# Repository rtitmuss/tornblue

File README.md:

# TornBlue - a bluetooth split keyboard

In this repo you can find information about the TornBlue a bluetooth split keyboard with SMT components. This is an iteration on the [Torn](https://github.com/rtitmuss/torn), which is a split keyboard using through hole components.

You can ask questions and get help on the [Torn Discord channel](https://discord.gg/mamAqNccju).

**WARNING: These files are provided as a reference for designing keyboard PCBs, without liability and without any guarantees regarding functionality. This is untested work in progress, really don't assume anything here will work.**

## Features

- nRF52840 using [zmk](https://zmk.dev/) keyboard firmware
- Battery charging for a 3.7v lithium rechargeable battery (JST-PH connector)
- 6x3 or 5x3 layout with detachable outer column
- 3 leds and 1 charging led
-  ([SOIC test clip footprint](https://hackaday.com/2019/06/13/soicbite-a-program-debug-connector-for-an-soic-test-clip/)) for programming
- Breakout with switchable 3.3v and gpios
- Battery level reported over BT
- Supports soldered Cherry MX compatible or Kailh Choc key switches
- Horizontal reset button (case friendly) 
- JLCPCB PCBA (pcb assembly); handsoldering required for underglow leds and JST-PH connector 

Optional features:

- Underglow leds 
- Optional Panasonic EVQWGD001 wheel encoders

## Parts required

- 2x assembled TornBlue Rev 1 PCBs
- 2x 3.7v lithium rechargeable battery with JST connector. **SAFETY NOTE: Only use a LiIon battery with over-charging and over-use protection. Check the battery polarity before connecting.**
- (Optional) 2x [JST-PH connector](https://www.electrokit.com/en/product/header-ph-2p-2mm-right-angle-smd/). 2mm pitch. Side entry. Surface-mounted.
- (Optional) 2 x [Panasonic EVQWGD001](https://www.aliexpress.com/wholesale?catId=0&initiative_id=SB_20210830111528&SearchText=Panasonic+EVQWGD001) wheel encoder
- (Optional) 12 x [WS2812B 5050 leds](https://www.aliexpress.com/wholesale?catId=0&initiative_id=SB_20210830111716&SearchText=WS2812B)
- (Optional) ST link v2 (or similar) and SOIC-8 test clip for programming the bootloader

## Build instructions

You can find full [build instructions](./build.md), and information for [different cases](./case/README.md).

## Components

The main components are:

- [Holyiot YJ-18010](http://www.holyiot.com/tp/2019042516322180424.pdf); this was chosen as it has castellated edges, which is easier hand soldering the module to the PCB.

- [XC6220](https://www.torexsemi.com/file/xc6220/XC6220.pdf); 3.3V voltage regulator to supply the Holyiot module.

- [TP4096](https://dlnmh9ip6v2uc.cloudfront.net/datasheets/Prototyping/TP4056.pdf) Li-Ion Battery Charger 

- [SRV05-4](https://www.onsemi.com/pdf/datasheet/srv05-4-d.pdf) ESD protection for the USB port
   
 - Other parts use 0805 and SOT-23 packages. These larger packages can be hand soldered and are similar sizes for a pleasing appearance. The parts have been laid out horizontally with a consistent polarity to simplify assembly.

## Reference designs

The following projects were used as reference designs.

- [ZMK hardware design guide](https://github.com/ebastler/zmk-designguide) (CERN Open Hardware Licence Version 2 - Permissive) - note the battery charging circuit might be unsafe, see this information about [TP4056](https://www.best-microcontroller-projects.com/tp4056.html)

- [isometria75](https://github.com/ebastler/isometria-75/tree/v2) (BSD 2-Clause License)

- [Unified USB type-C PCB](https://github.com/ebastler/unified-usb-pcb) (BSD 2-Clause License)

- [Nice!Nano](https://nicekeyboards.com/docs/nice-nano/pinout-schematic)

- [nRFMicro](https://github.com/joric/nrfmicro/wiki) (Public domain)

- [Adafruit nRF52840](https://learn.adafruit.com/introducing-the-adafruit-nrf52840-feather/downloads) (Creative Commons Attribution, Share-Alike)

## Showcase

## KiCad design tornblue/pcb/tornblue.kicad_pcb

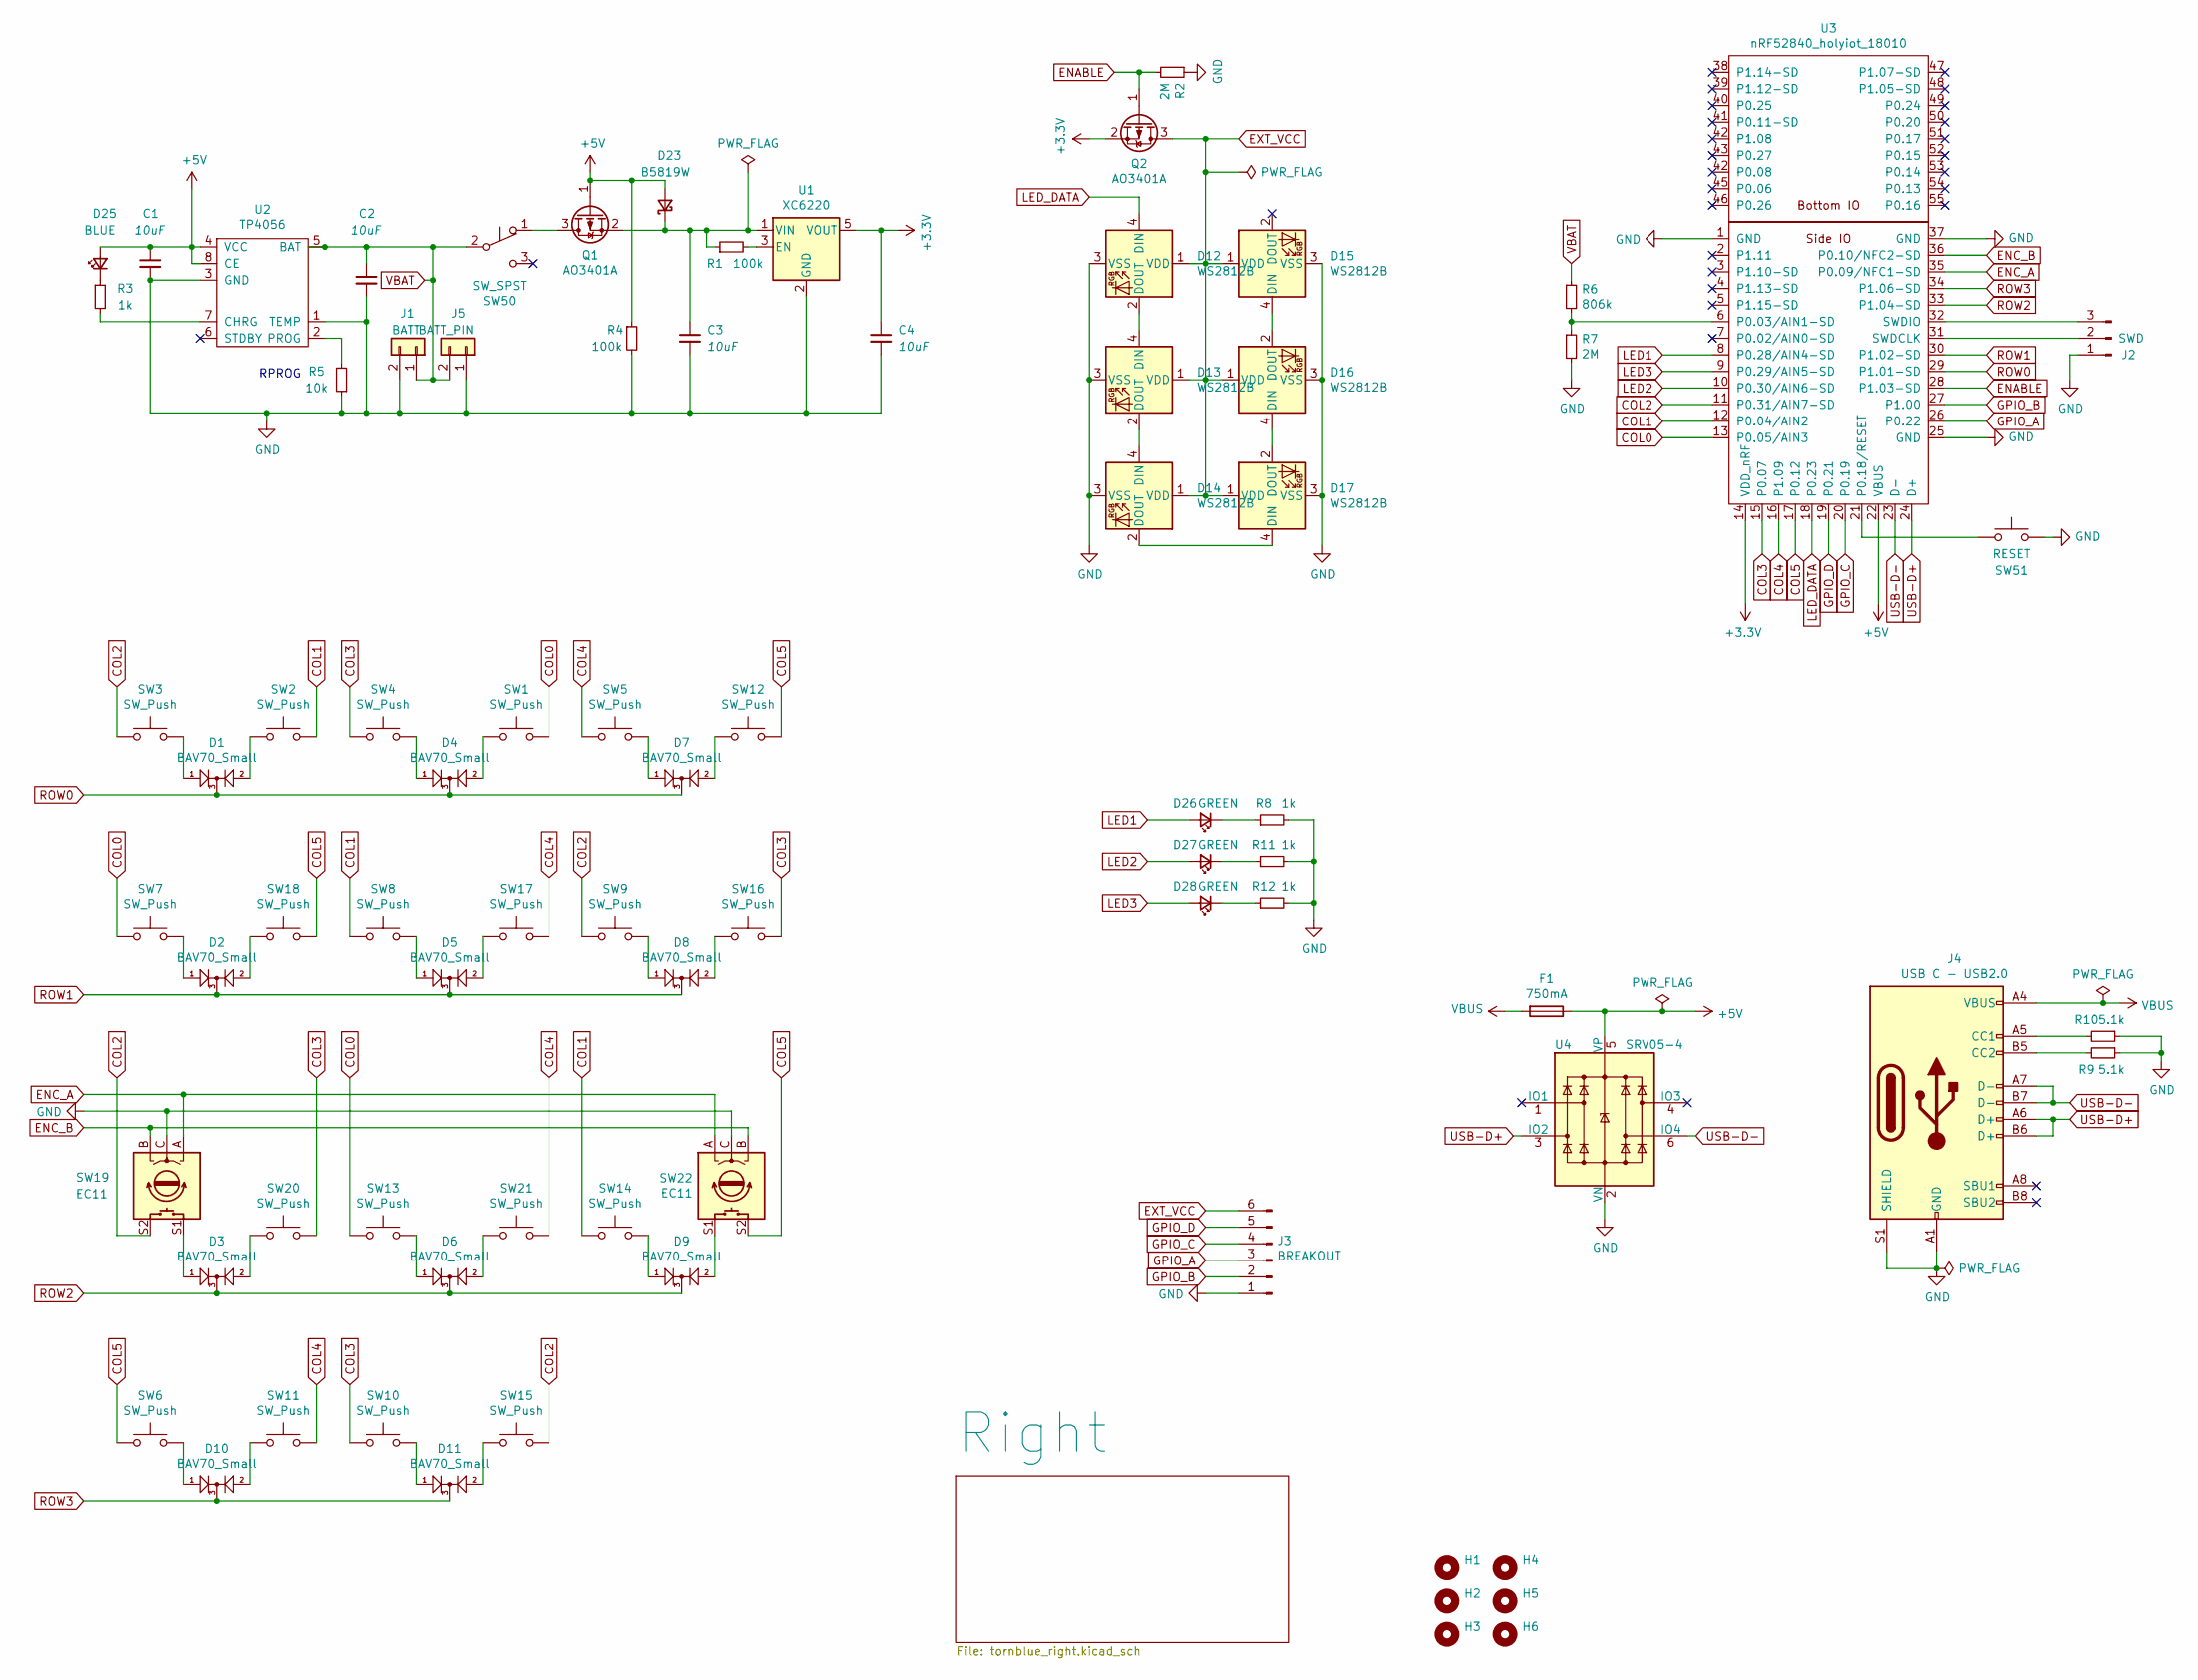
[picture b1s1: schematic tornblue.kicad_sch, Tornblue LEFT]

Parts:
C1, C2, C3, C4: 10uF; D_0805_2012Metric; LCSC C15850
D1, D2, D3, D4, D5, D6, D7, D8, D9, D10, D11: BAV70_Small; SOT-23; LCSC C68978
D12, D13, D14, D15, D16, D17: WS2812B; LED_WS2812B_PLCC4_5.0x5.0mm_P3.2mm; LCSC C2761795
D23: B5819W; D_SOD-123; LCSC C8598
D25: BLUE; LED_0805_2012Metric; LCSC C99870
D26, D27, D28: GREEN; LED_0805_2012Metric; LCSC C397047
F1: 750mA; Fuse_1206_3216Metric; LCSC C328915
H1, H2, H3, H4: MountingHole; MountingHole_3.2mm_M3_DIN965_Pad
H5, H6: MountingHole; MountingHole_3.2mm_M3_DIN965_Pad_Slot
J1: BATT; JST_PH_S2B-PH-SM4-TB_1x02-1MP_P2.00mm_Horizontal; LCSC C295747
J2: SWD; SOIC_clipProgSmall
J3: BREAKOUT; PinHeader_1x06_P1.27mm_Vertical
J4: USB C - USB2.0; USB_C_Receptacle_XKB_U262-16XN-4BVC11; LCSC C167321
J5: BATT_PIN; PinHeader_1x02_P2.54mm_Vertical
Q1, Q2: AO3401A; SOT-23; LCSC C15127
R1, R4: 100k; R_0805_2012Metric; LCSC C17407
R2, R7: 2M; R_0805_2012Metric; LCSC C26112
R3, R8, R11, R12: 1k; R_0805_2012Metric; LCSC C17513
R5: 10k; R_0805_2012Metric; LCSC C17414
R6: 806k; R_0805_2012Metric; LCSC C63494
R9, R10: 5.1k; R_0805_2012Metric; LCSC C27834
SW1, SW2, SW3, SW4, SW5, SW6, SW7, SW8, SW9, SW10, SW11, SW12, SW13, SW14, SW15, SW16, SW17, SW18, SW20, SW21: SW_Push; MX_PG1350_optional
SW19, SW22: EC11; MX_PG1350_EVQWGD001_LR_optional
SW50: SW_SPST; SW_SPDT_PCM12; LCSC C221841
SW51: RESET; SW_SPST_TS24CA; LCSC C393942
U1: XC6220; SOT-23-5; LCSC C86534
U2: TP4056; SOIC-8-1EP_3.9x4.9mm_P1.27mm_EP2.29x3mm_ThermalVias; LCSC C16581
U3: nRF52840_holyiot_18010; LCSC nRF52840_holyiot_18010
U4: SRV05-4; SOT-23-6; LCSC C85364

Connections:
+3V3: C4.1, Q2.2 (S), U1.5 (VOUT), U3.14 (VDD_nRF)
+5V: C1.1, D23.2 (A), D25.2 (A), F1.1, Q1.1 (G), R4.1, U2.4 (VCC), U2.8 (CE), U3.22 (VBUS), U4.5 (VP)
COL0: SW1.1, SW7.1, SW13.1, U3.13 (P0.05/AIN3)
COL1: SW2.1, SW8.1, SW14.1, U3.12 (P0.04/AIN2)
COL2: SW3.1, SW9.1, SW15.1, SW19.S2, U3.11 (P0.31/AIN7-SD)
COL3: SW4.1, SW10.1, SW16.1, SW20.1, U3.15 (P0.07)
COL4: SW5.1, SW11.1, SW17.1, SW21.1, U3.16 (P1.09)
COL5: SW6.1, SW12.1, SW18.1, SW22.S2, U3.17 (P0.12)
ENABLE: Q2.1 (G), R2.2, U3.28 (P1.03-SD)
ENC_A: SW19.A, SW22.A, U3.35 (P0.09/NFC1-SD)
ENC_B: SW19.B, SW22.B, U3.36 (P0.10/NFC2-SD)
EXT_VCC: D12.1 (VDD), D13.1 (VDD), D14.1 (VDD), D15.1 (VDD), D16.1 (VDD), D17.1 (VDD), J3.6, Q2.3 (D)
GND: C1.2, C2.2, C3.2, C4.2, D12.3 (VSS), D13.3 (VSS), D14.3 (VSS), D15.3 (VSS), D16.3 (VSS), D17.3 (VSS), J1.2, J2.1, J3.1, J4.A1 (GND), J4.A12 (GND), J4.B1 (GND), J4.B12 (GND), J4.S1 (SHIELD), J5.1, R2.1, R4.2, R5.1, R7.2, R8.2, R9.1, R10.1, R11.2, R12.2, SW19.C, SW22.C, SW51.2, U1.2 (GND), U2.1 (TEMP), U2.3 (GND), U3.1 (GND), U3.25 (GND), U3.37 (GND), U4.2 (VN)
GPIO_A: J3.3, U3.26 (P0.22)
GPIO_B: J3.2, U3.27 (P1.00)
GPIO_C: J3.4, U3.20 (P0.19)
GPIO_D: J3.5, U3.19 (P0.21)
LED1: D26.2 (A), U3.8 (P0.28/AIN4-SD)
LED2: D27.2 (A), U3.10 (P0.30/AIN6-SD)
LED3: D28.2 (A), U3.9 (P0.29/AIN5-SD)
LED_DATA: D12.4 (DIN), U3.18 (P0.23)
unnamed: C3.1, D23.1 (K), Q1.2 (S), R1.1, U1.1 (VIN)
unnamed: D1.1 (A1), SW3.2
unnamed: D1.2 (A2), SW2.2
unnamed: D2.1 (A1), SW7.2
unnamed: D2.2 (A2), SW18.2
unnamed: D3.1 (A1), SW19.S1
unnamed: D3.2 (A2), SW20.2
unnamed: D4.1 (A1), SW4.2
unnamed: D4.2 (A2), SW1.2
unnamed: D5.1 (A1), SW8.2
unnamed: D5.2 (A2), SW17.2
unnamed: D6.1 (A1), SW13.2
unnamed: D6.2 (A2), SW21.2
unnamed: D7.1 (A1), SW5.2
unnamed: D7.2 (A2), SW12.2
unnamed: D8.1 (A1), SW9.2
unnamed: D8.2 (A2), SW16.2
unnamed: D9.1 (A1), SW14.2
unnamed: D9.2 (A2), SW22.S1
unnamed: D10.1 (A1), SW6.2
unnamed: D10.2 (A2), SW11.2
unnamed: D11.1 (A1), SW10.2
unnamed: D11.2 (A2), SW15.2
unnamed: D12.2 (DOUT), D13.4 (DIN)
unnamed: D13.2 (DOUT), D14.4 (DIN)
unnamed: D14.2 (DOUT), D17.4 (DIN)
unnamed: D15.4 (DIN), D16.2 (DOUT)
unnamed: D16.4 (DIN), D17.2 (DOUT)
unnamed: D25.1 (K), R3.1
unnamed: D26.1 (K), R8.1
unnamed: D27.1 (K), R11.1
unnamed: D28.1 (K), R12.1
unnamed: J2.2, U3.31 (SWDCLK)
unnamed: J2.3, U3.32 (SWDIO)
unnamed: J4.A5 (CC1), R10.2
unnamed: J4.B5 (CC2), R9.2
unnamed: Q1.3 (D), SW50.1 (A)
unnamed: R1.2, U1.3 (EN)
unnamed: R3.2, U2.7 (CHRG)
unnamed: R5.2, U2.2 (PROG)
unnamed: R6.2, R7.1, U3.6 (P0.03/AIN1-SD)
unnamed: SW51.1, U3.21 (P0.18/RESET)
ROW0: D1.3 (K), D4.3 (K), D7.3 (K), U3.29 (P1.01-SD)
ROW1: D2.3 (K), D5.3 (K), D8.3 (K), U3.30 (P1.02-SD)
ROW2: D3.3 (K), D6.3 (K), D9.3 (K), U3.33 (P1.04-SD)
ROW3: D10.3 (K), D11.3 (K), U3.34 (P1.06-SD)
USB-D+: J4.A6 (D+), J4.B6 (D+), U3.24 (D+), U4.3 (IO2)
USB-D-: J4.A7 (D-), J4.B7 (D-), U3.23 (D-), U4.6 (IO4)
VBAT: C2.1, J1.1, J5.2, R6.1, SW50.2 (B), U2.5 (BAT)
VBUS: F1.2, J4.A4 (VBUS), J4.A9 (VBUS), J4.B4 (VBUS), J4.B9 (VBUS)

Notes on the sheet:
RPROG

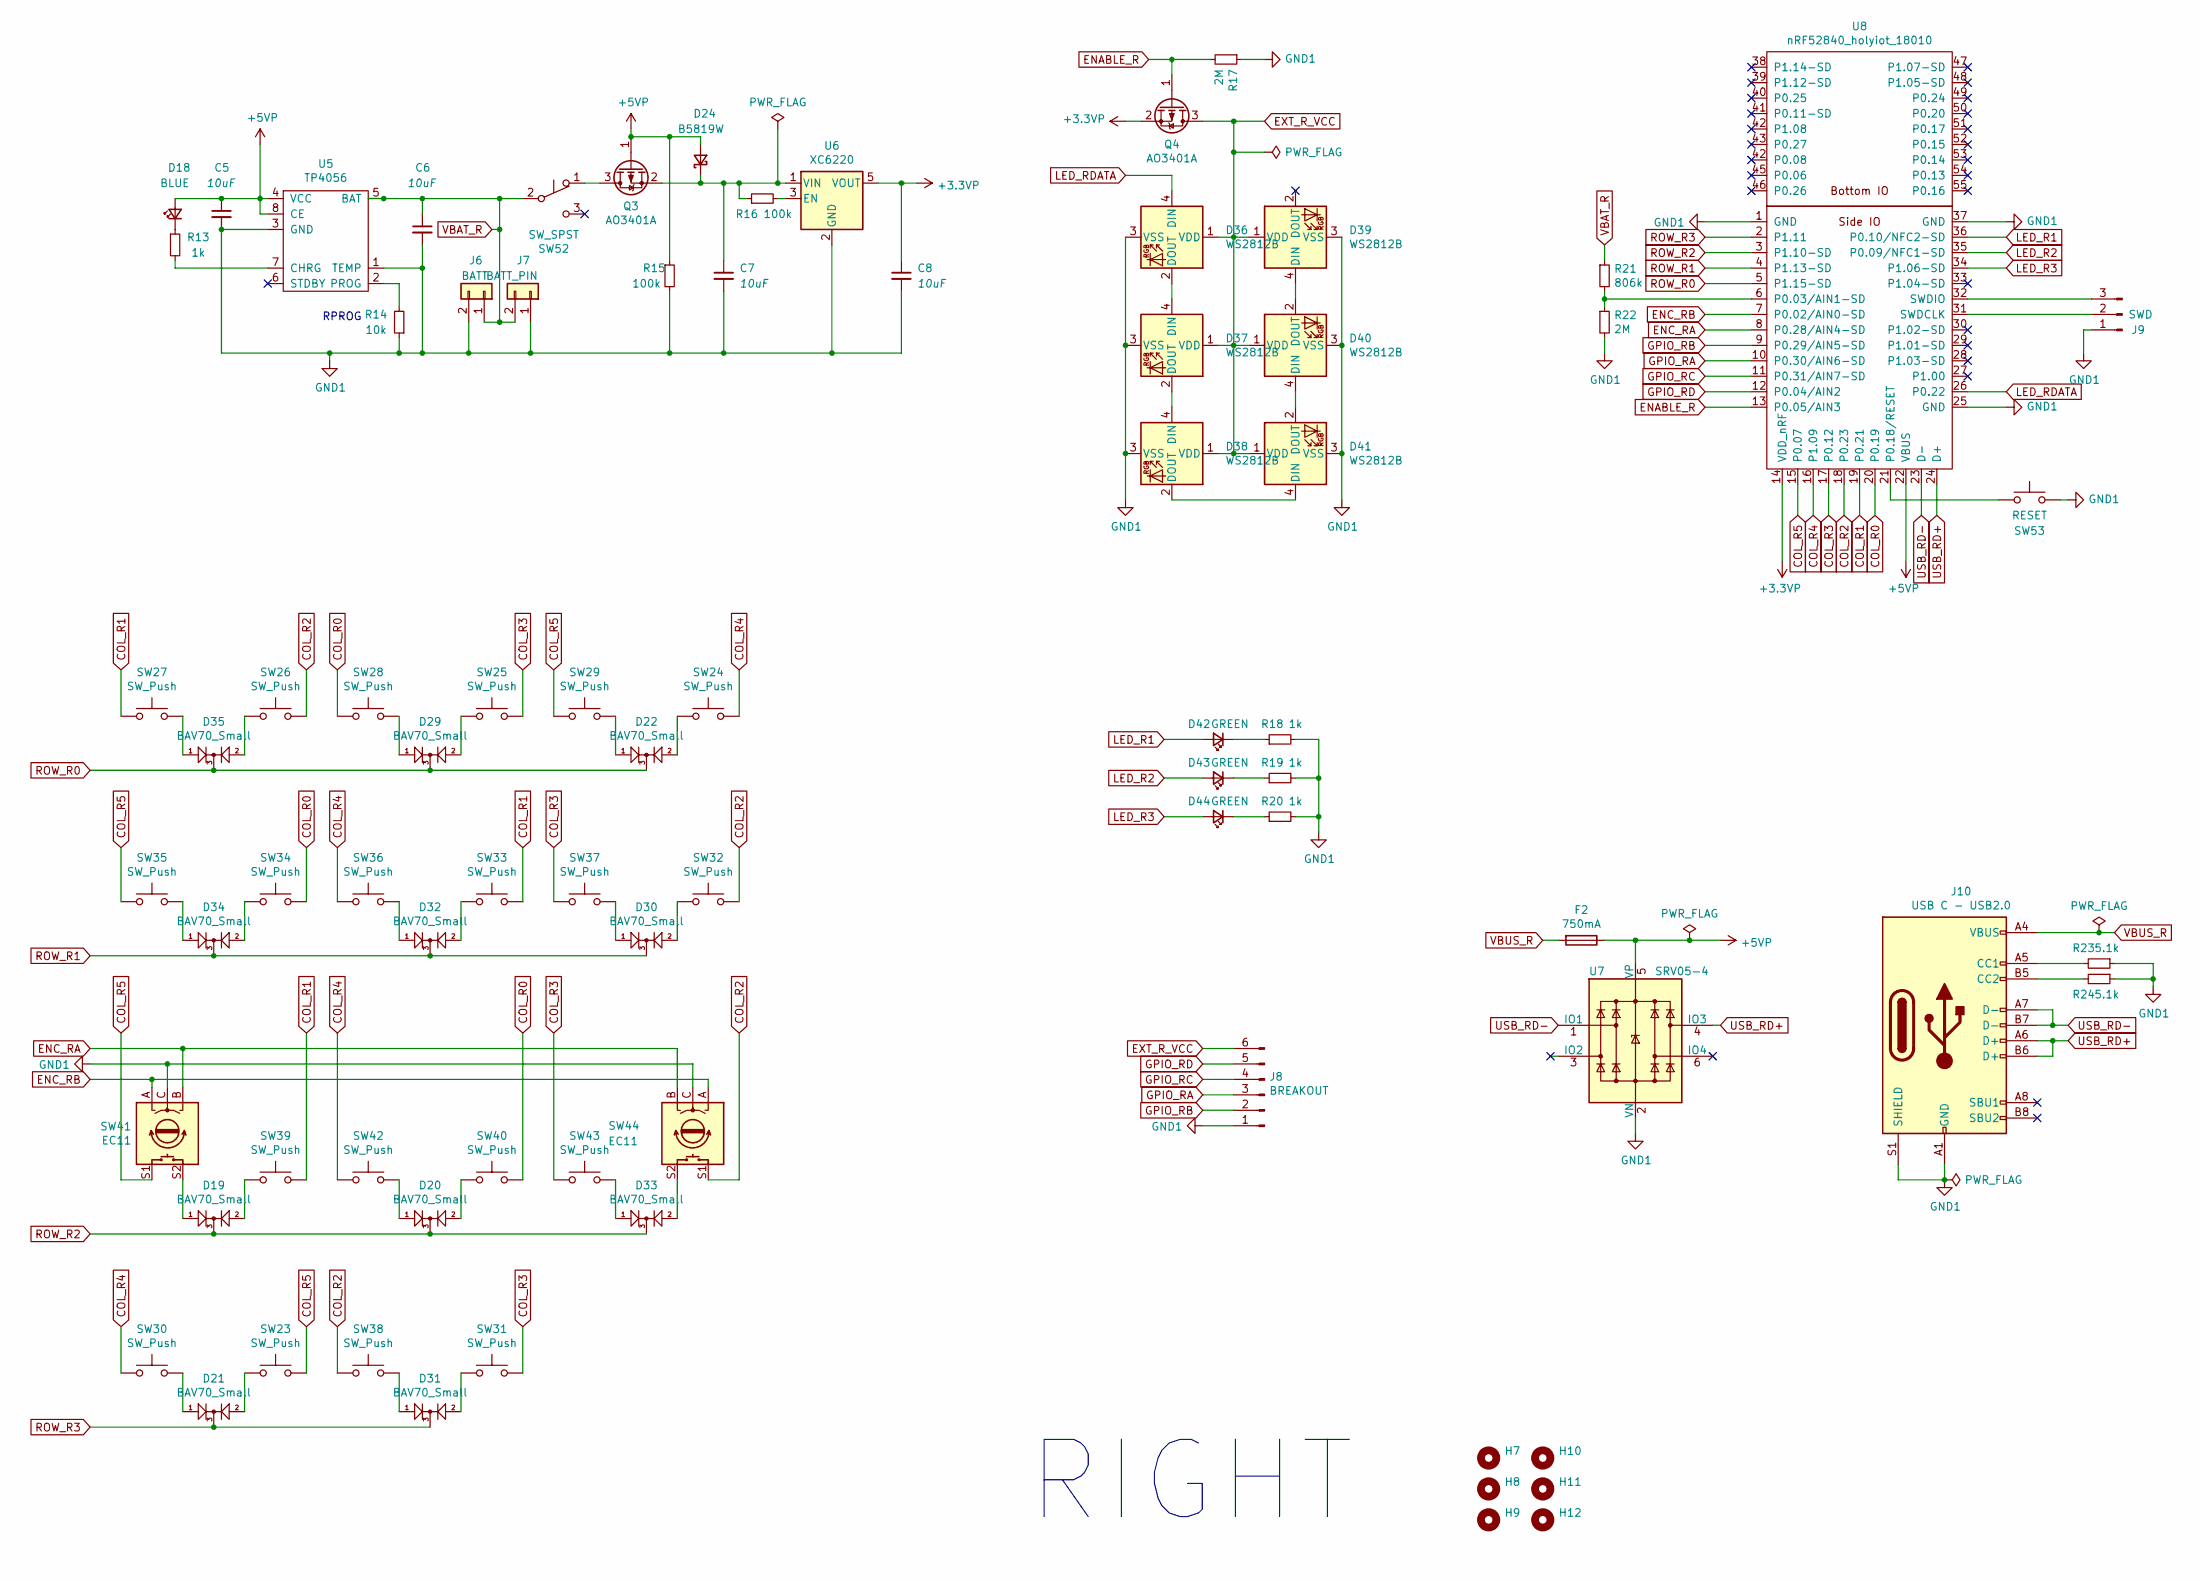
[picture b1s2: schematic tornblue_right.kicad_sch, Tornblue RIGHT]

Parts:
C5, C6, C7, C8: 10uF; D_0805_2012Metric; LCSC C15850
D18: BLUE; LED_0805_2012Metric; LCSC C99870
D19, D20, D21, D22, D29, D30, D31, D32, D33, D34, D35: BAV70_Small; SOT-23; LCSC C68978
D24: B5819W; D_SOD-123; LCSC C8598
D36, D37, D38, D39, D40, D41: WS2812B; LED_WS2812B_PLCC4_5.0x5.0mm_P3.2mm; LCSC C2761795
D42, D43, D44: GREEN; LED_0805_2012Metric; LCSC C397047
F2: 750mA; Fuse_1206_3216Metric; LCSC C328915
H7, H8, H9, H10: MountingHole; MountingHole_3.2mm_M3_DIN965_Pad
H11, H12: MountingHole; MountingHole_3.2mm_M3_DIN965_Pad_Slot
J6: BATT; JST_PH_S2B-PH-SM4-TB_1x02-1MP_P2.00mm_Horizontal; LCSC C295747
J7: BATT_PIN; PinHeader_1x02_P2.54mm_Vertical
J8: BREAKOUT; PinHeader_1x06_P1.27mm_Vertical
J9: SWD; SOIC_clipProgSmall
J10: USB C - USB2.0; USB_C_Receptacle_XKB_U262-16XN-4BVC11; LCSC C167321
Q3, Q4: AO3401A; SOT-23; LCSC C15127
R13, R18, R19, R20: 1k; R_0805_2012Metric; LCSC C17513
R14: 10k; R_0805_2012Metric; LCSC C17414
R15, R16: 100k; R_0805_2012Metric; LCSC C17407
R17, R22: 2M; R_0805_2012Metric; LCSC C26112
R21: 806k; R_0805_2012Metric; LCSC C63494
R23, R24: 5.1k; R_0805_2012Metric; LCSC C27834
SW23, SW24, SW25, SW26, SW27, SW28, SW29, SW30, SW31, SW32, SW33, SW34, SW35, SW36, SW37, SW38, SW39, SW40, SW42, SW43: SW_Push; MX_PG1350_optional
SW41, SW44: EC11; MX_PG1350_EVQWGD001_UD_optional
SW52: SW_SPST; SW_SPDT_PCM12; LCSC C221841
SW53: RESET; SW_SPST_TS24CA; LCSC C393942
U5: TP4056; SOIC-8-1EP_3.9x4.9mm_P1.27mm_EP2.29x3mm_ThermalVias; LCSC C16581
U6: XC6220; SOT-23-5; LCSC C86534
U7: SRV05-4; SOT-23-6; LCSC C85364
U8: nRF52840_holyiot_18010; LCSC nRF52840_holyiot_18010

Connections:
+3.3VP: C8.1, Q4.2 (S), U6.5 (VOUT), U8.14 (VDD_nRF)
+5VP: C5.1, D18.2 (A), D24.2 (A), F2.1, Q3.1 (G), R15.1, U5.4 (VCC), U5.8 (CE), U7.5 (VP), U8.22 (VBUS)
COL_R0: SW28.1, SW34.1, SW40.1, U8.20 (P0.19)
COL_R1: SW27.1, SW33.1, SW39.1, U8.19 (P0.21)
COL_R2: SW26.1, SW32.1, SW38.1, SW44.S1, U8.18 (P0.23)
COL_R3: SW25.1, SW31.1, SW37.1, SW43.1, U8.17 (P0.12)
COL_R4: SW24.1, SW30.1, SW36.1, SW42.1, U8.16 (P1.09)
COL_R5: SW23.1, SW29.1, SW35.1, SW41.S1, U8.15 (P0.07)
ENABLE_R: Q4.1 (G), R17.2, U8.13 (P0.05/AIN3)
ENC_RA: SW41.B, SW44.B, U8.8 (P0.28/AIN4-SD)
ENC_RB: SW41.A, SW44.A, U8.7 (P0.02/AIN0-SD)
EXT_R_VCC: D36.1 (VDD), D37.1 (VDD), D38.1 (VDD), D39.1 (VDD), D40.1 (VDD), D41.1 (VDD), J8.6, Q4.3 (D)
GND1: C5.2, C6.2, C7.2, C8.2, D36.3 (VSS), D37.3 (VSS), D38.3 (VSS), D39.3 (VSS), D40.3 (VSS), D41.3 (VSS), J6.2, J7.1, J8.1, J9.1, J10.A1 (GND), J10.A12 (GND), J10.B1 (GND), J10.B12 (GND), J10.S1 (SHIELD), R14.1, R15.2, R17.1, R18.2, R19.2, R20.2, R22.2, R23.1, R24.1, SW41.C, SW44.C, SW53.2, U5.1 (TEMP), U5.3 (GND), U6.2 (GND), U7.2 (VN), U8.1 (GND), U8.25 (GND), U8.37 (GND)
GPIO_RA: J8.3, U8.10 (P0.30/AIN6-SD)
GPIO_RB: J8.2, U8.9 (P0.29/AIN5-SD)
GPIO_RC: J8.4, U8.11 (P0.31/AIN7-SD)
GPIO_RD: J8.5, U8.12 (P0.04/AIN2)
LED_R1: D42.2 (A), U8.36 (P0.10/NFC2-SD)
LED_R2: D43.2 (A), U8.35 (P0.09/NFC1-SD)
LED_R3: D44.2 (A), U8.34 (P1.06-SD)
LED_RDATA: D36.4 (DIN), U8.26 (P0.22)
unnamed: C7.1, D24.1 (K), Q3.2 (S), R16.1, U6.1 (VIN)
unnamed: D18.1 (K), R13.1
unnamed: D19.1 (A1), SW41.S2
unnamed: D19.2 (A2), SW39.2
unnamed: D20.1 (A1), SW42.2
unnamed: D20.2 (A2), SW40.2
unnamed: D21.1 (A1), SW30.2
unnamed: D21.2 (A2), SW23.2
unnamed: D22.1 (A1), SW29.2
unnamed: D22.2 (A2), SW24.2
unnamed: D29.1 (A1), SW28.2
unnamed: D29.2 (A2), SW25.2
unnamed: D30.1 (A1), SW37.2
unnamed: D30.2 (A2), SW32.2
unnamed: D31.1 (A1), SW38.2
unnamed: D31.2 (A2), SW31.2
unnamed: D32.1 (A1), SW36.2
unnamed: D32.2 (A2), SW33.2
unnamed: D33.1 (A1), SW43.2
unnamed: D33.2 (A2), SW44.S2
unnamed: D34.1 (A1), SW35.2
unnamed: D34.2 (A2), SW34.2
unnamed: D35.1 (A1), SW27.2
unnamed: D35.2 (A2), SW26.2
unnamed: D36.2 (DOUT), D37.4 (DIN)
unnamed: D37.2 (DOUT), D38.4 (DIN)
unnamed: D38.2 (DOUT), D41.4 (DIN)
unnamed: D39.4 (DIN), D40.2 (DOUT)
unnamed: D40.4 (DIN), D41.2 (DOUT)
unnamed: D42.1 (K), R18.1
unnamed: D43.1 (K), R19.1
unnamed: D44.1 (K), R20.1
unnamed: J9.2, U8.31 (SWDCLK)
unnamed: J9.3, U8.32 (SWDIO)
unnamed: J10.A5 (CC1), R23.2
unnamed: J10.B5 (CC2), R24.2
unnamed: Q3.3 (D), SW52.1 (A)
unnamed: R13.2, U5.7 (CHRG)
unnamed: R14.2, U5.2 (PROG)
unnamed: R16.2, U6.3 (EN)
unnamed: R21.2, R22.1, U8.6 (P0.03/AIN1-SD)
unnamed: SW53.1, U8.21 (P0.18/RESET)
ROW_R0: D22.3 (K), D29.3 (K), D35.3 (K), U8.5 (P1.15-SD)
ROW_R1: D30.3 (K), D32.3 (K), D34.3 (K), U8.4 (P1.13-SD)
ROW_R2: D19.3 (K), D20.3 (K), D33.3 (K), U8.3 (P1.10-SD)
ROW_R3: D21.3 (K), D31.3 (K), U8.2 (P1.11)
USB_RD+: J10.A6 (D+), J10.B6 (D+), U7.4 (IO3), U8.24 (D+)
USB_RD-: J10.A7 (D-), J10.B7 (D-), U7.1 (IO1), U8.23 (D-)
VBAT_R: C6.1, J6.1, J7.2, R21.1, SW52.2 (B), U5.5 (BAT)
VBUS_R: F2.2, J10.A4 (VBUS), J10.A9 (VBUS), J10.B4 (VBUS), J10.B9 (VBUS)

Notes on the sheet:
RIGHT
RPROG

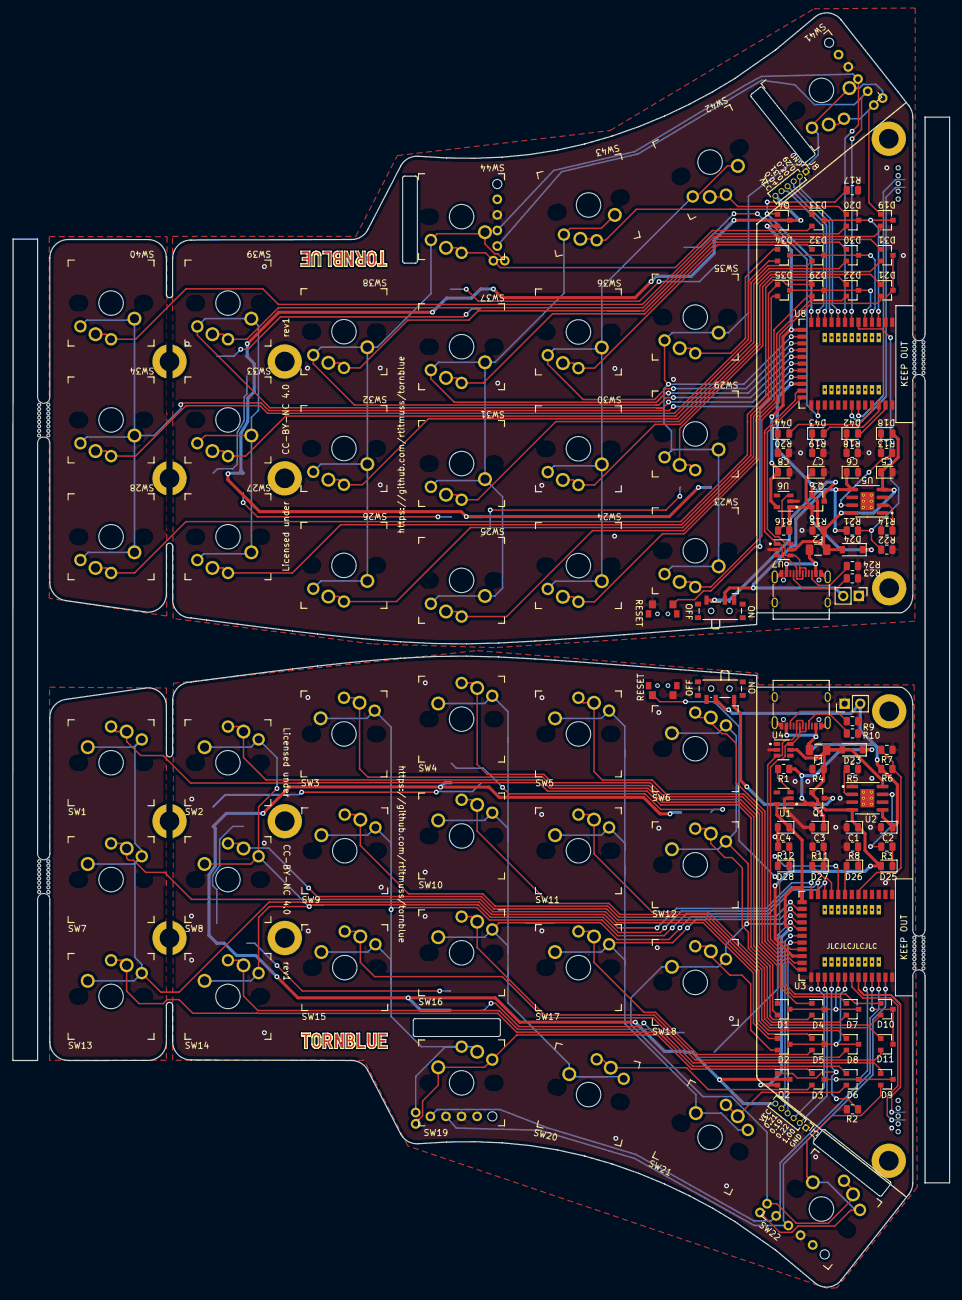
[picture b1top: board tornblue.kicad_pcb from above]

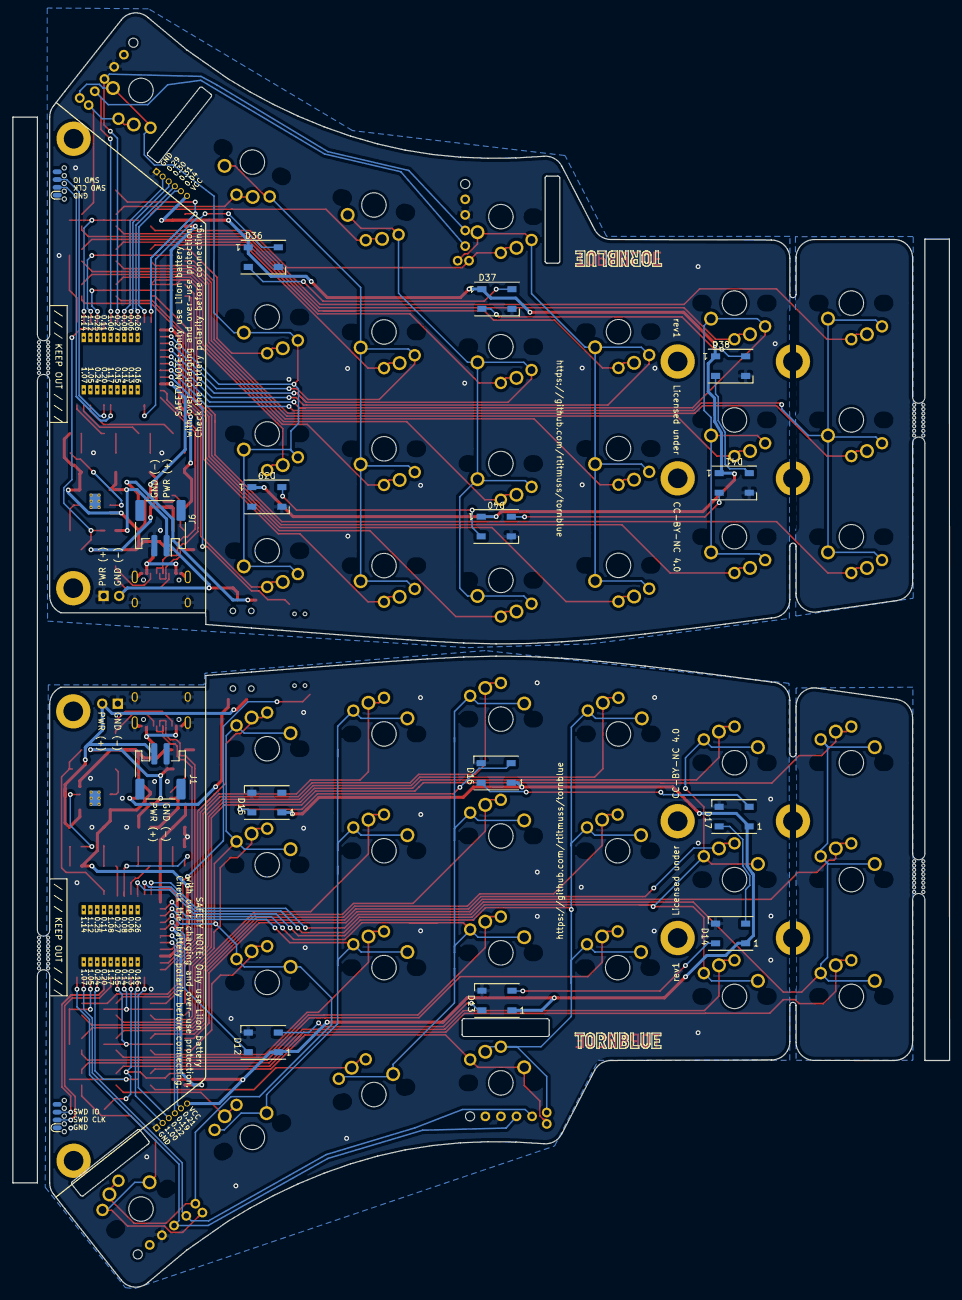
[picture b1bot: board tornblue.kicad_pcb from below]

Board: 2 copper layers, 152.7 x 207.8 mm, 164 parts (16 on the bottom side), 142 nets.

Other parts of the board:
mouse-bite-5mm-slot, mouse-bite-5mm-slot#2, mouse-bite-5mm-slot#3, mouse-bite-5mm-slot#4: VAL**; mouse-bite-5mm-slot

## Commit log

2021-09-09 Tornblue rev0
2021-09-18 Initial build instructions
2021-09-28 Add 3d printed case files
2021-09-29 Add 6 column wedge case
2021-09-29 Use m3 mounting holes
2021-09-29 Smooth board outline
2021-09-29 Change to lower profile reset switch
2021-09-30 Removed support for Kailh MX sockets
    It is not possible to include options for Kailh MX sockets, underglow
    LEDS and Panasonic EVQWGD001 encoder on the same PCB.
2021-09-30 Move holyiot module up 1.5mm
2021-10-10 Rearrange BAV70 grid
2021-10-10 Move BAV70 grid up 0.5mm
2021-10-10 Fix EVQWGD001 footprint
2021-10-10 Move underglow leds up 1mm
2021-10-10 Add battery pins + silk screen fixes
2021-10-10 Add power switch
2021-10-10 Silk screen fixes
2021-10-16 Add right edgecuts
2021-10-16 Add right schematic
2021-10-16 Placed components on the right side
2021-10-16 Add zones
2021-10-16 Fix encoder rotation
2021-10-18 Routing key matrix
2021-11-21 Finish layout, via placement and silk screen
2021-11-21 Fix kibot config
    Command:
    ~/.local/bin/kicad-exports -d docs -b tornblue.kicad_pcb -e tornblue.sch -c kibot.yaml
2021-11-21 Add elecrow files
2021-11-27 Update to kicad 6
2021-11-28 Curved traces
2021-11-28 Update reset button
2021-12-01 Fix 3d models without changing footrprint pads
2021-12-01 Add powered by zmk silk
2021-12-01 Add extra mousebites
2021-12-07 checkpoint
2022-01-01 Update kibot for KiCad 6 and start elcrow bom
    Slightly hacky but running on osx:
    DYLD_FALLBACK_LIBRARY_PATH=/Applications/KiCad/KiCad.app/Contents/Frameworks:/usr/local/opt/python\@3.8/Frameworks/Python.framework/ PYTHONPATH=/Applications/KiCad/KiCad.app/Contents/Frameworks/Pytho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
2022-01-04 Elecrow BOM
2022-01-04 Fix gerbers for jlcpcb
    Need to remove the hatched ground fill to prevent the jlcpcb
    processing from timing out
2022-01-04 Fab file for elecrow
2022-01-05 Add holes to the ground plane
2022-01-09 Download datasheets with kibot
2022-01-09 r1 PCBA files for jlcpcb and elecrow
2022-01-09 Move pcb files
2022-01-09 r1 step file
2022-01-09 Add fusion 360 model
2022-04-02 Update instructions
2022-04-02 Add images
2022-04-02 Add Discord channel
2022-04-02 Updated fusion360 design file
2022-04-02 Updated files for 3d printed case
2022-04-02 Remove old dxf files
2022-04-02 Fix bootloader filename
2022-04-23 Add interlocking joint
2022-05-01 Fix case links
2022-07-04 Add stacked acrylic plate case
2022-08-13 Fix stacked-acrylic images
2022-08-13 Resize images
2022-08-13 Add mini wedge case
2022-10-20 clarify bootloader instructions
2023-02-09 Remove hatched ground fill
    This causes jlcpcb site to timeout processing the gerbers, and you
    can't really see the hatched effect on the finished keyboard anyway.
2023-02-09 Add kibot as github workflow
2023-02-09 Add kibot config
2023-02-09 Disable kibot plugins
    - 3d models are missing (git submodules, or licensing)
    - plugins that crash
    - plugins that hang
2023-02-25 Add 6 column 3d printed cases

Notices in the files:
tornblue/pcb/tornblue.kicad_pcb:
Licensed under CC-BY-NC 4.0 rev1
rev1 Licensed under CC-BY-NC 4.0
